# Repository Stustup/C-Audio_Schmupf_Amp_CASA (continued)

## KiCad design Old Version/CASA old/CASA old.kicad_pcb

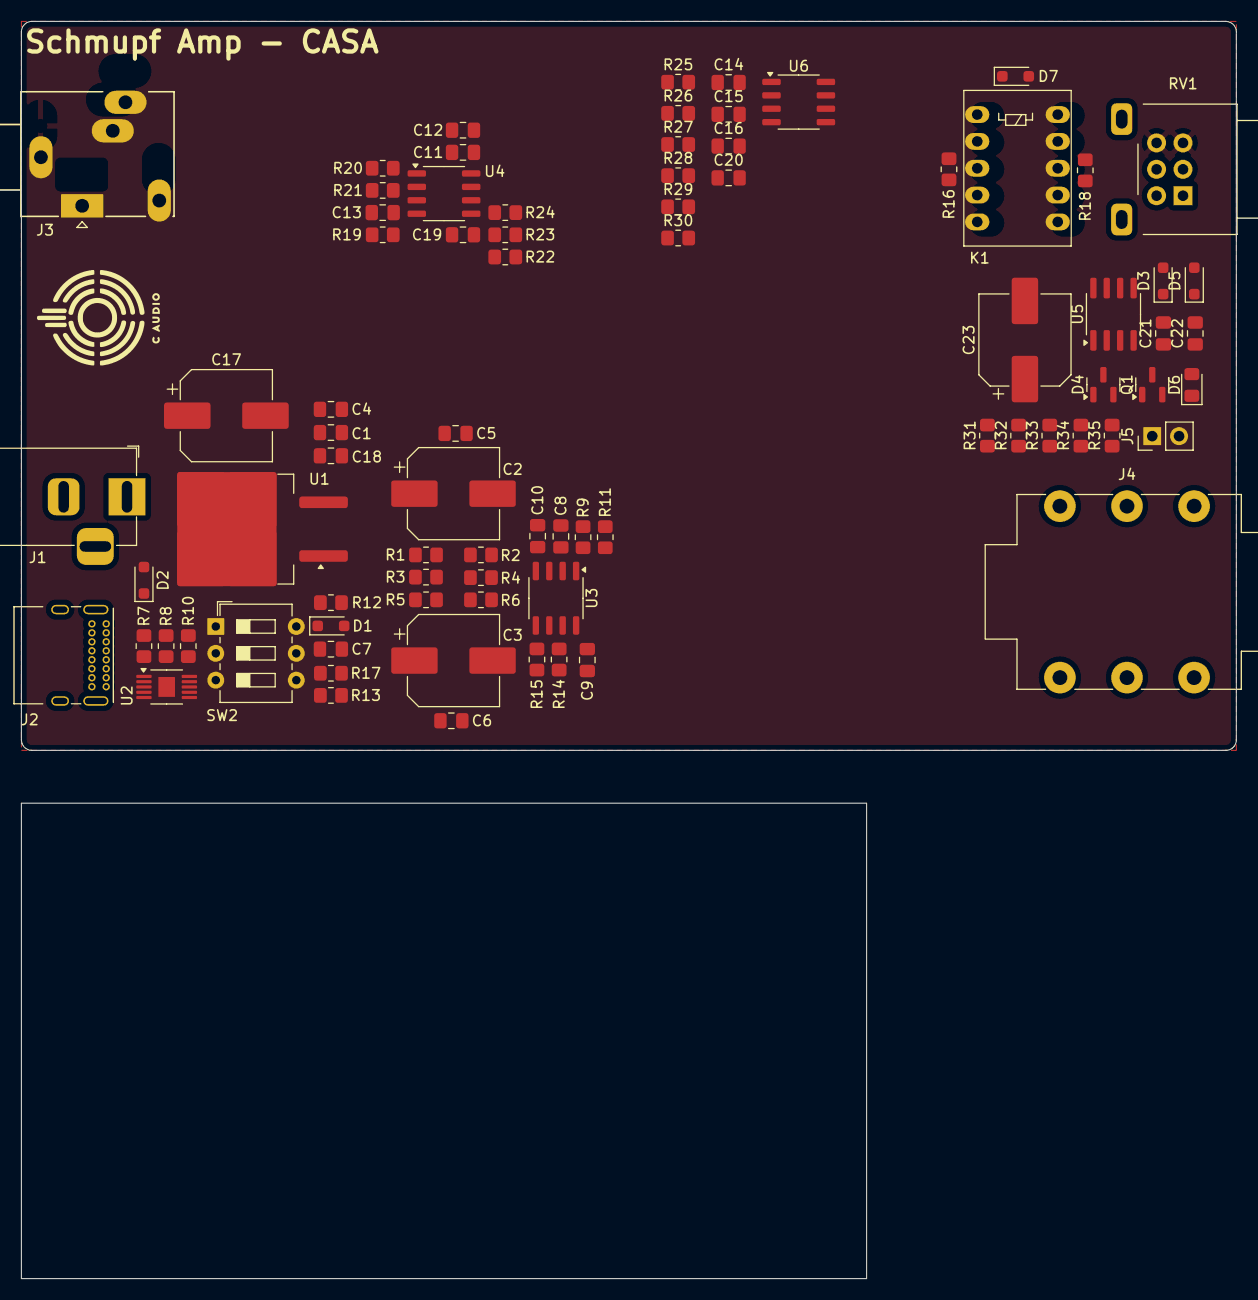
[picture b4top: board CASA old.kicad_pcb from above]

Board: 2 copper layers, 115.0 x 119.0 mm, 80 parts (0 on the bottom side), 47 nets, no tracks yet.

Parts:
C1: 10u 35V; C_0805_2012Metric_Pad1.18x1.45mm_HandSolder
C2, C3: 470u; CP_Elec_8x10.5
C4, C5, C6, C8, C9, C10, C11, C12, C13, C14, C15, C16, C18, C21: 100n; C_0805_2012Metric_Pad1.18x1.45mm_HandSolder
C7, C22: 10u; C_0805_2012Metric_Pad1.18x1.45mm_HandSolder
C17: 470u 35V; CP_Elec_8x10.5
C19, C20: 100p; C_0805_2012Metric_Pad1.18x1.45mm_HandSolder
C23: 100u 35V; CP_Elec_8x10.5
D1, D3, D7: 1N4001; D_SOD-323_HandSoldering
D2: D_Small; D_SOD-323_HandSoldering
D4: 5V6 Zener; SOT-23
D5: 1N4148; D_SOD-323_HandSoldering
D6: LED_grn; D_0805_2012Metric_Pad1.15x1.40mm_HandSolder
J1: Barrel_Jack_Switch; BarrelJack_Horizontal
J2: USB_C_Receptacle; USB_C_Receptacle_GCT_USB4085
J3: Audio In; Jack_3.5mm_Ledino_KB3SPRS_Horizontal
J4: Audio Out; Jack_6.35mm_Neutrik_NMJ6HFD2-AU_Horizontal
J5: Manual Relay; PinHeader_1x02_P2.54mm_Vertical
K1: FRT5; Relay_DPDT_FRT5
Q1: 2N7002; SOT-23
R1, R2, R3, R4, R5, R6: 33k; R_0805_2012Metric_Pad1.20x1.40mm_HandSolder
R7: 1k; R_0805_2012Metric_Pad1.20x1.40mm_HandSolder
R8, R16, R18, R33, R34, R35: 10k; R_0805_2012Metric_Pad1.20x1.40mm_HandSolder
R9, R11: 330R; R_0805_2012Metric_Pad1.20x1.40mm_HandSolder
R10: 24k; R_0805_2012Metric_Pad1.20x1.40mm_HandSolder
R12, R31: 240R; R_0805_2012Metric_Pad1.20x1.40mm_HandSolder
R13: 1k5; R_0805_2012Metric_Pad1.20x1.40mm_HandSolder
R14, R15, R23, R24, R29, R30: 1R; R_0805_2012Metric_Pad1.20x1.40mm_HandSolder
R17: 3k2; R_0805_2012Metric_Pad1.20x1.40mm_HandSolder
R19, R20, R25, R26: 470R; R_0805_2012Metric_Pad1.20x1.40mm_HandSolder
R21, R27: 100k; R_0805_2012Metric_Pad1.20x1.40mm_HandSolder
R22, R28: 940R; R_0805_2012Metric_Pad1.20x1.40mm_HandSolder
R32: 2k; R_0805_2012Metric_Pad1.20x1.40mm_HandSolder
RV1: 10kA; Potentiometer_Alps_RK09L_Double_Horizontal
SW2: Voltage Select; SW_DIP_SPSTx03_Slide_6.7x9.18mm_W7.62mm_P2.54mm_LowProfile
U1: LM317_TO-263; TO-263-2
U2: CH224K; HVSSOP-10-1EP_3x3mm_P0.5mm_EP1.57x1.88mm
U3: OPA1688; SO-8_3.9x4.9mm_P1.27mm
U4, U6: OPA1662; SO-8_3.9x4.9mm_P1.27mm
U5: LM317L_SO8; SOIC-8_3.9x4.9mm_P1.27mm

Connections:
+12V: C1.1, C4.1, D1.1 (K), D2.1 (K), D3.2 (A), D6.2 (A), J2.A4 (VBUS), J2.A9 (VBUS), J2.B4 (VBUS), J2.B9 (VBUS), R7.1, R8.1, R31.1, U1.3 (VI), U5.2 (VO), U5.3 (VO), U5.6 (VO), U5.7 (VO)
+12V_2: D5.1 (K), D7.1 (K), K1.1, R33.1
/Adj V-reg: C7.1, R12.2, SW2.1, SW2.2, U1.1 (ADJ)
/Amp_In_L: R20.1, RV1.2
/Amp_In_R: R26.1, RV1.5
/In_L: J3.T, K1.8
/In_R: J3.R, K1.3
/Out_L: J4.T, R23.2, R24.2
/Out_R: J4.R, R29.2, R30.2
/USBC PD: SW2.3, U2.9 (CFG1)
/r_mute: D7.2 (A), J5.1, K1.10, Q1.3 (D), R35.2
GND: C1.2, C3.2, C4.2, C6.2, C7.2, C11.2, C13.2, C14.2, C16.2, C17.2, C18.2, C21.2, C22.2, C23.2, J1.2, J2.A1 (GND), J2.A12 (GND), J2.B1 (GND), J2.B12 (GND), J5.2, Q1.2 (S), R2.2, R4.2, R6.2, R10.2, R13.2, R17.2, R32.2, R34.2, U2.11 (GND), U4.4 (V-), U6.4 (V-)
InGND: C2.2, C3.1, C5.2, C6.1, C9.2, C10.1, C12.2, C13.1, C15.2, C16.1, J3.S, R1.2, R2.1, R3.2, R4.1, R5.2, R6.1, R9.1, R19.1, R21.1, R25.1, R27.1, RV1.3, RV1.6
unnamed: D2.2 (A), J1.1
unnamed: D4.1 (A), D5.2 (A), Q1.1 (G), R34.1
unnamed: C23.1, D4.3 (K), R33.2
unnamed: D6.1 (K), R35.1
unnamed: J2.A5 (CC1), U2.7 (CC1)
unnamed: J2.B5 (CC2), U2.6 (CC2)
unnamed: K1.2, R16.2, RV1.4
unnamed: K1.4, R16.1
unnamed: K1.7, R18.1
unnamed: K1.9, R18.2, RV1.1
unnamed: R10.1, SW2.4
unnamed: R13.1, SW2.5
unnamed: R14.1, U3.7
unnamed: R17.1, SW2.6
unnamed: J2.A6 (D+), J2.B6 (D+), U2.5 (DM)
unnamed: J2.A7 (D-), J2.B7 (D-), U2.4 (DP)
unnamed: R8.2, U2.8 (VBUS)
unnamed: R7.2, U2.1 (VDD)
unnamed: R9.2, U3.3 (+)
unnamed: R11.1, U3.2 (-)
unnamed: R15.1, U3.1, U3.5 (+)
unnamed: C8.1, C9.1, U3.8 (V+)
unnamed: C8.2, C10.2, U3.4 (V-)
unnamed: R20.2, R21.2, U4.3 (+)
unnamed: C19.1, R19.2, R22.1, U4.2 (-)
unnamed: C19.2, R22.2, R23.1, U4.1, U4.5 (+)
unnamed: R24.1, U4.6 (-), U4.7
unnamed: C22.1, R31.2, R32.1, U5.4 (ADJ)
unnamed: R26.2, R27.2, U6.3 (+)
unnamed: C20.1, R25.2, R28.1, U6.2 (-)
unnamed: C20.2, R28.2, R29.1, U6.1, U6.5 (+)
unnamed: R30.1, U6.6 (-), U6.7
OpGND: J4.S, R11.2, R14.2, R15.2, U3.6 (-)
VDD: C2.1, C5.1, C11.1, C12.1, C14.1, C15.1, C17.1, C18.1, C21.1, D1.2 (A), D3.1 (K), R1.1, R3.1, R5.1, R12.1, U1.2 (VO), U4.8 (V+), U5.1 (VI), U6.8 (V+)

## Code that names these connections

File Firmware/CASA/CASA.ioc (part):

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Mcu.Name=STM32F030F4Px
Mcu.Package=TSSOP20
Mcu.UserName=STM32F030F4Px
PA0.GPIOParameters=PinState,GPIO_PuPd,GPIO_Label
PA0.GPIO_Label=ext_PSU-en
PA0.GPIO_PuPd=GPIO_PULLDOWN
PA0.PinState=GPIO_PIN_RESET
PA0.Signal=GPIO_Output
PA1.GPIOParameters=PinState,GPIO_PuPd,GPIO_Label
PA1.GPIO_Label=ext_mute
PA1.GPIO_PuPd=GPIO_PULLDOWN
PA1.PinState=GPIO_PIN_SET
PA1.Signal=GPIO_Output
PA10.Mode=I2C
PA10.Signal=I2C1_SDA
PA13.Mode=Serial_Wire
PA13.Signal=SYS_SWDIO
PA14.Mode=Serial_Wire
PA14.Signal=SYS_SWCLK
PA2.GPIOParameters=PinState,GPIO_PuPd,GPIO_Label
PA2.GPIO_Label=ext_gain
PA2.GPIO_PuPd=GPIO_PULLDOWN
PA2.PinState=GPIO_PIN_RESET
PA2.Signal=GPIO_Output
PA3.GPIOParameters=PinState,GPIO_PuPd,GPIO_Label
PA3.GPIO_Label=ext_input
PA3.GPIO_PuPd=GPIO_PULLDOWN
PA3.PinState=GPIO_PIN_RESET
PA3.Signal=GPIO_Output
PA5.GPIOParameters=PinState,GPIO_PuPd,GPIO_Label,GPIO_ModeDefaultOutputPP
PA5.GPIO_Label=frontLED_grn
PA5.GPIO_ModeDefaultOutputPP=GPIO_MODE_OUTPUT_PP
PA5.GPIO_PuPd=GPIO_PULLDOWN
PA5.PinState=GPIO_PIN_RESET
PA5.Signal=GPIO_Output
PA6.GPIOParameters=PinState,GPIO_PuPd,GPIO_Label,GPIO_ModeDefaultOutputPP
PA6.GPIO_Label=frontLED_blu
PA6.GPIO_ModeDefaultOutputPP=GPIO_MODE_OUTPUT_PP
PA6.GPIO_PuPd=GPIO_PULLDOWN
PA6.PinState=GPIO_PIN_RESET
PA6.Signal=GPIO_Output
PA7.GPIOParameters=PinState,GPIO_PuPd,GPIO_Label,GPIO_ModeDefaultOutputPP
PA7.GPIO_Label=frontLED_red
PA7.GPIO_ModeDefaultOutputPP=GPIO_MODE_OUTPUT_PP
PA7.GPIO_PuPd=GPIO_PULLDOWN
PA7.PinState=GPIO_PIN_RESET
PA7.Signal=GPIO_Output
PA9.Mode=I2C
PA9.Signal=I2C1_SCL
PF0-OSC_IN.GPIOParameters=GPIO_PuPd,GPIO_Label,GPIO_ModeDefaultEXTI
PF0-OSC_IN.GPIO_Label=btn_gain
PF0-OSC_IN.GPIO_ModeDefaultEXTI=GPIO_MODE_IT_FALLING
PF0-OSC_IN.GPIO_PuPd=GPIO_NOPULL
PF0-OSC_IN.Signal=GPXTI0
PF1-OSC_OUT.GPIOParameters=GPIO_PuPd,GPIO_Label,GPIO_ModeDefaultEXTI
PF1-OSC_OUT.GPIO_Label=btn_input
PF1-OSC_OUT.GPIO_ModeDefaultEXTI=GPIO_MODE_IT_FALLING
PF1-OSC_OUT.GPIO_PuPd=GPIO_NOPULL
PF1-OSC_OUT.Signal=GPXTI1
RCC.SYSCLKFreq_VALUE=48000000
RCC.SYSCLKSource=RCC_SYSCLKSOURCE_PLLCLK
board=custom

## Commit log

2025-12-11 added project
2025-12-11 changed relays to 12V for easier power distribution
2025-12-11 new project structure
2025-12-11 added 3D Model of case and pcb
2025-12-11 Added Text indicators and TP designators
2025-12-11 Added simple readme and docs
2025-12-11 dunno
2025-12-15 improved routing and added TODOS
2025-12-15 Finished power wiring
2025-12-15 added vias to signal paths
2026-01-21 Finmished front board
2026-03-26 combined GNDs and finalized egrbers
2026-06-09 Finalized placement, pcb and schematic. Firmware WIP
